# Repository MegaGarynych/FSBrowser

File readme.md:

# FSBrowser

### This project is discontinued. I recommend you to go to [FSBrowserNG](https://github.com/gmag11/FSBrowserNG). It has same functionality and uses a faster web server library.

## Introduction
I wanted to add a standard environment for all my ESP8266 based projects to be able to configure them via web browser to avoid code editing when I need to change some settings like SSID, password, etc.

I found [John Lassen's WebConfig project](http://www.john-lassen.de/index.php/projects/esp-8266-arduino-ide-webconfig) to almost fit my needs. It uses a simple but powerful web interface with dynamic data using [microAJAX](https://code.google.com/archive/p/microajax/). I've added some dynamic data using [Links2004](https://github.com/Links2004)'s [WebSockets library](https://github.com/Links2004/arduinoWebSockets).

So, I tried to fork it. Original WebConfig project stores web pages on PROGMEM, but I was recently using SPIFFS on ESP8266 and I think it is a good way to store web content. I found I was not the first to think this when I noticed about [FSBrowser](https://github.com/esp8266/Arduino/tree/master/libraries/ESP8266WebServer/examples/FSBrowser) example in [ESP8266WebServer](https://github.com/esp8266/Arduino/tree/master/libraries/ESP8266WebServer) library.

This example code has a great bonus. A text editor (based on [ACE](https://ace.c9.io/)) with syntax highligth that can be used to edit html on board directly. I found a [bug](https://github.com/esp8266/Arduino/pull/1771) on it (already sent to [esp8266/Arduino](https://github.com/esp8266/Arduino/) repository) and, when fixed, noticed how usefull this editor is.

My code is a fork of both projects, and has become a start framework for my future projects.

I only have to add more HTML data and some funtions to show dynamic data in order to adapt it to any other task.

It has integrated NTP syncronization based on my own [NTPClient library](https://github.com/gmag11/NtpClient), that can be configured via this Web interface too.

Configuration is stored on SPIFFS too, in a JSON file. So, it recovers config during boot.

Implemented OTA Update with Arduino IDE and Web interface.

Web access can be protected with Basic HTTP Authentication.

#### Notice that Basic HTTP Authentication alone is not suitable to protect data over Internet. It allows recovery of user and password via sniffing and does not encrypt data flow. It is valid to give a first protection and may be a good solution combining it with strong VPN. Take this in account when connecting it to public networks or Internet.

## WiFi connection
I've implemented a way to turn ESP8266 into AP mode so I can set WiFi config when prior WiFi is not available. It is done by setting IO pin 4 to high status during boot. This pin is configurable by a `#define.` __You must ensure it is connected to GND to allow it to connect to a router__.

AP Mode is also started when `loadConfig()` finds no config file (config.json). This is so to help first use without needind to hardcode user and password.

WiFi connection to router is confirmed via LED on IO pin #0 as soon an IP address is got. Same LED is used to confirm AP mode by flashing 3 times. LED ping can be configured in `config.h`.

## Schematics

## How to use it

After compile and flash into ESP8266 you need to upload SPIFFS data using [download tool](https://github.com/esp8266/arduino-esp8266fs-plugin/releases/download/0.2.0/ESP8266FS-0.2.0.zip) for Arduino IDE. Check [SPIFFS doc](https://github.com/esp8266/Arduino/blob/master/doc/filesystem.md) for details.

* `http://ip_address/admin.html` takes you to main configuration GUI.
* `http://ip_address/edit` contains code editor. Any file stored in SPIFFS may be loaded here and saved using `CTRL+S` command.
* `http://ip_address/update` allows remote update through WEB.
* `http://ip_address/` includes an example info page that shows how to get realtime data from ESP. You may change this to adapt to your project.

## TODO

- ~~HTTP Authentication~~ HTTP Basic authentication implemented. Will try to improve to a more secure mechanism.
- ~~OTA update via web interface~~ MD5 cheching added.
- ~~MD5 check of uploaded firmware~~
- ~~Configuration protection~~
- ~~HTTPS (in evaluation).~~ *Not possible with ESP8266 yet*
- ~~Integration of editor in admin.html~~
- ~~Convert code to classes and try to design a library to add all this functionality easily. *Evaluating if this is worth, but anyway it is not currently a priority*~~ *Check my newer [FSBrowserNG](https://github.com/gmag11/FSBrowserNG) repository*

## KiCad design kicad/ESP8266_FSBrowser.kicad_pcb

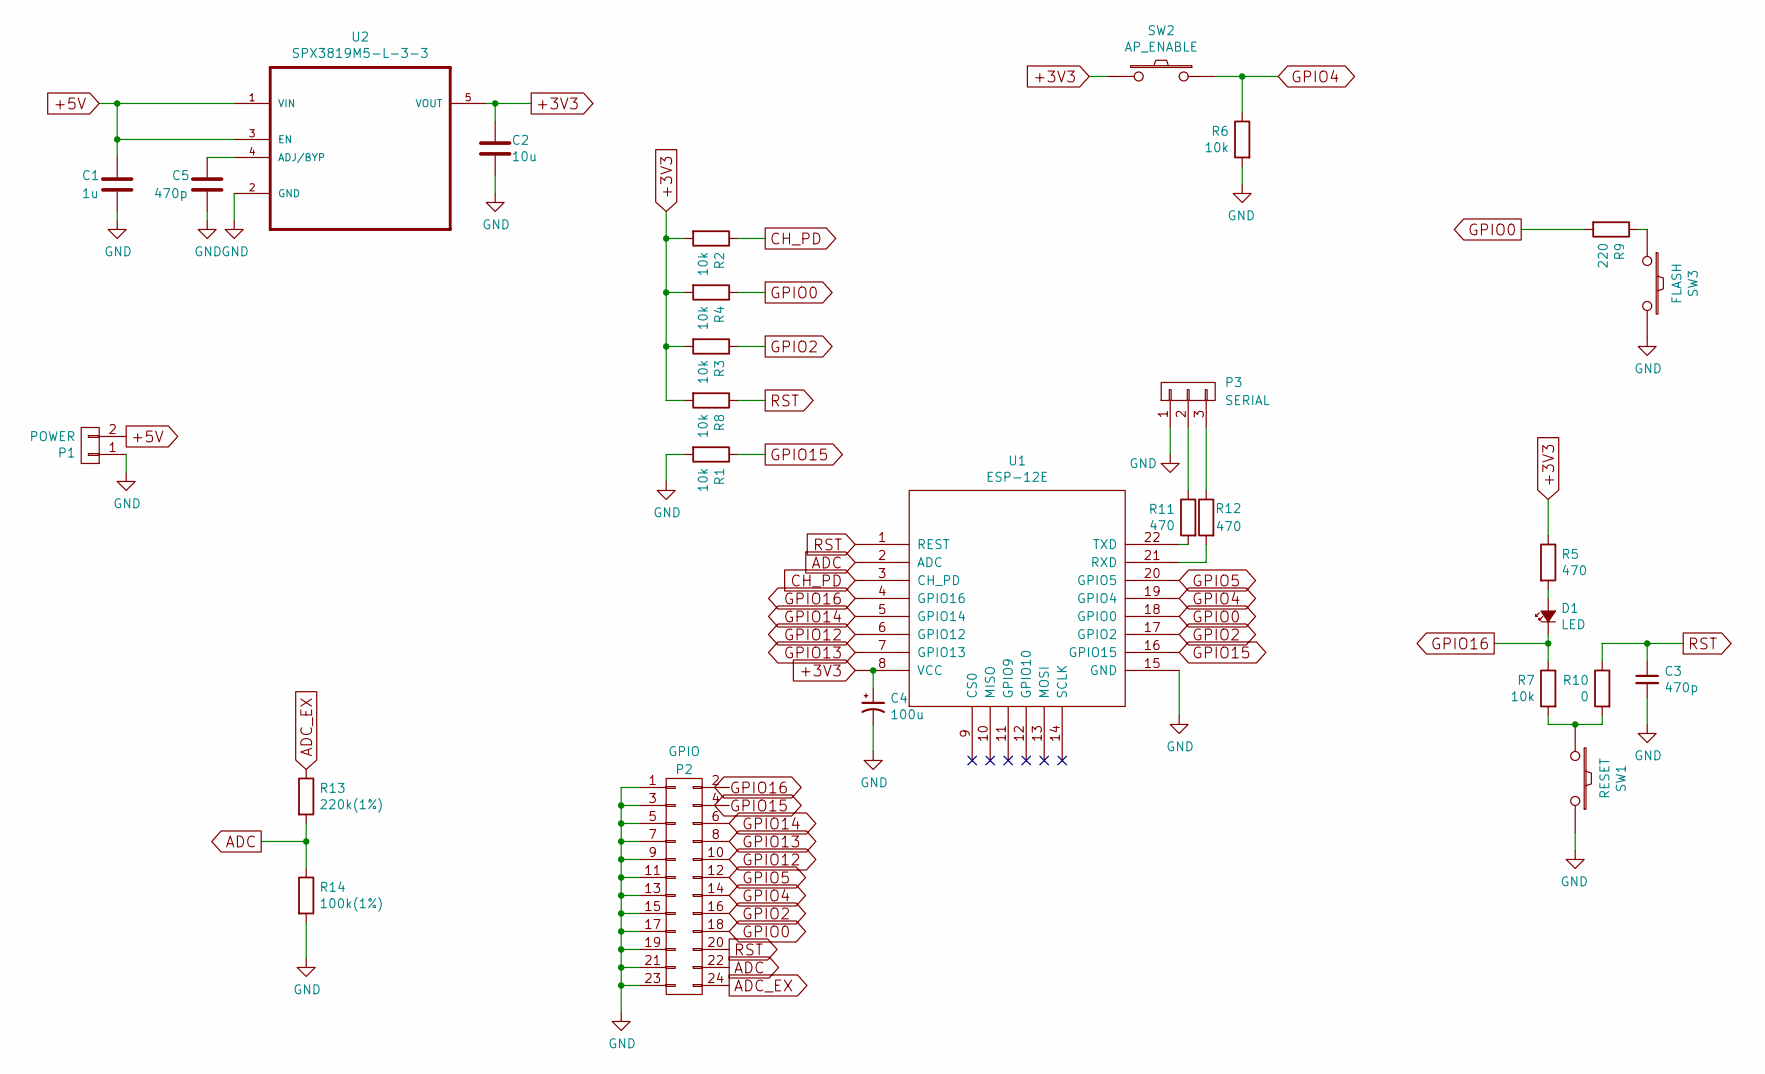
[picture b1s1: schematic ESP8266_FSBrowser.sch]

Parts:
C1: 1u; C_0603
C2: 10u; C_0603
C3, C5: 470p; C_0603
C4: 100u; c_elec_6.3x5.8
D1: LED; LED-3MM
P1: POWER; Pin_Header_Straight_1x02
P2: GPIO; Pin_Header_Straight_2x12
P3: SERIAL; Pin_Header_Straight_1x03
R1, R2, R3, R4, R6, R7, R8: 10k; R_0603
R5, R11, R12: 470; R_0603
R9: 220; R_0603
R10: 0; R_0603
R13: 220k(1%); R_0603
R14: 100k(1%); R_0603
SW1: RESET; SW_SPST_B3S-1000
SW2: AP_ENABLE; SW_SPST_B3S-1000
SW3: FLASH; SW_SPST_B3S-1000
U1: ESP-12E
U2: SPX3819M5-L-3-3; SOT-23-5

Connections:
+3V3: C2.1, R2.2, R3.2, R4.2, R5.1, R8.2, SW2.2, U1.8 (VCC), U2.5 (VOUT)
+5V: C1.1, P1.2, U2.1 (VIN), U2.3 (EN)
ADC: P2.22, R13.2, R14.1, U1.2 (ADC)
ADC_EX: P2.24, R13.1
CH_PD: R2.1, U1.3 (CH_PD)
GND: C1.2, C2.2, C3.2, C4.2, C5.2, P1.1, P2.1, P2.3, P2.5, P2.7, P2.9, P2.11, P2.13, P2.15, P2.17, P2.19, P2.21, P2.23, P3.1, R1.2, R6.2, R14.2, SW1.1, SW3.2, U1.15 (GND), U2.2 (GND)
GPIO0: P2.18, R4.1, R9.2, U1.18 (GPIO0)
GPIO2: P2.16, R3.1, U1.17 (GPIO2)
GPIO4: P2.14, R6.1, SW2.1, U1.19 (GPIO4)
GPIO5: P2.12, U1.20 (GPIO5)
GPIO12: P2.10, U1.6 (GPIO12)
GPIO13: P2.8, U1.7 (GPIO13)
GPIO14: P2.6, U1.5 (GPIO14)
GPIO15: R1.1, U1.16 (GPIO15)
GPIO16: D1.1 (K), R7.1, U1.4 (GPIO16)
unnamed: C5.1, U2.4 (ADJ/BYP)
unnamed: D1.2 (A), R5.2
unnamed: P3.2, R11.1
unnamed: P3.3, R12.1
unnamed: R9.1, SW3.1
unnamed: R7.2, R10.2, SW1.2
unnamed: R11.2, U1.22 (TXD)
unnamed: R12.2, U1.21 (RXD)
RST: C3.1, P2.20, R8.1, R10.1, U1.1 (REST)

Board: 2 copper layers, 28 parts (0 on the bottom side), 24 nets, no tracks yet.

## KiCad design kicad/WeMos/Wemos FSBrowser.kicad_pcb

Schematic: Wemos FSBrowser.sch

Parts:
P1: POWER; Pin_Header_Straight_1x02
P2: TEMP_SENS; Pin_Header_Straight_1x03
R1: 10k; Resistor_Horizontal_RM7mm
R2: 4k7; Resistor_Horizontal_RM7mm
SW1: AP_MODE; SW_SPST_B3S-1000
U1: WeMos_mini; D1_mini_board

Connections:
+3V3: P2.1, R2.1, SW1.2, U1.16
/+5V: P1.2, U1.1
GND: P1.1, P2.3, R1.2, U1.2
GPIO4: R1.1, SW1.1, U1.5
GPIO12: P2.2, R2.2, U1.13

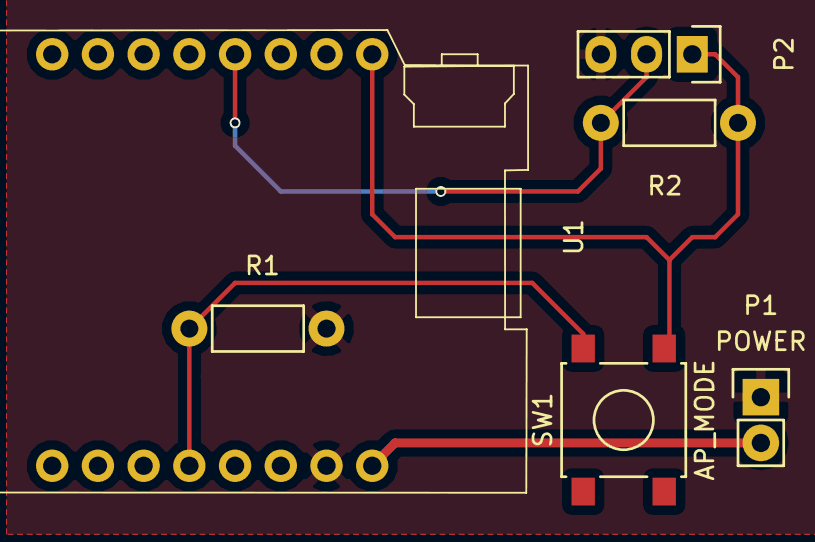
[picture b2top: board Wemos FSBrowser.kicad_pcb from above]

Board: 2 copper layers, 6 parts (0 on the bottom side), 5 nets.

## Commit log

2016-03-05 Connection control
2016-03-05 no message
2016-03-11 Remove AP in startup. It's difficult to do simultaneous AP + STA when there are conncetion problems due to channel scan.
2016-03-11 Clean up disabled functions and variables
2016-03-13 Add WebSocket to send time and date in real time. It works!!!
2016-03-13 Fix editor
2016-03-14 Fix HTML files. Fix editor
2016-03-14 Add more fields to info page
2016-03-14 Update default config
2016-03-14 Reenable AP config if Digital Input 4 is high to be able to reset configuration in case of wrong WiFi configuration
2016-03-15 Add some comments to functions and variables. Filter debug strings with preprocessor directives.
2016-03-26 Add flash function to be used when AP mode
2016-03-26 Add readme.md
2016-03-27 Fix MDNS
2016-03-28 Add schematics
2016-03-28 Add Fritzing breadboard image
2016-04-02 Adjust SPIFFS
2016-04-02 Review html forms. Fix navigation button
2016-04-02 Add built in LED support
2016-04-02 Recover external LED
2016-04-02 Implement OTA Update
2016-04-04 Reconnect websocket when clicking refresh button
2016-04-04 Add remote restart
2016-04-04 Add dim LED
2016-04-05 Return to fix LED. Add flash when disconnected.
2016-04-05 First Basic HTTP Authentication implementation
2016-04-05 Authenticate all
2016-04-05 Filter DEBUG messages
2016-04-06 Store user and passwd on SPIFFS
2016-04-06 Add restart option
2016-04-06 Fix JSON secret example file
2016-04-06 Add link to editor
2016-04-06 Disable HTTP auth if some error ocurrs reading secret file
2016-04-07 Add HTTP Auth config to Web interface
2016-04-07 Fix auth data completion via web interface
2016-04-08 Try configurable LED. Commented lines
2016-04-08 Add led activity when send file to web browser
2016-04-08 Disable OTA password due to Arduino IDE not asking for it
2016-04-08 Implement HTTP update server
2016-04-10 Disable update auth
2016-04-10 Integrate HTTP Updater on server code. TODO: Check if update is possible before uploading. i.e. ESP01 does not allow remote update due to limited flash space.
2016-04-11 Check remote update is possible in this board
2016-04-11 Make DEBUG directives file specific
2016-04-11 Comment code
2016-04-11 Add config protection. Config files are not available to download trhu web browser --> Error 401 Unauthorized.
2016-04-11 Comment more code
2016-04-13 Specific code for ESP01. OTA not possible. Integrated LED connected to TX and only pins 0 and 2 available
2016-04-14 add OTA update to system.html
2016-04-14 Correct navigation
2016-04-14 Correct free space check before web OTA update
2016-04-14 Correct button width
2016-04-14 Add MD5 library
2016-04-14 Add MD5 processing when updating firmware
2016-04-15 Complete MD5 for update
2016-04-15 Restructure DEBUG directives
2016-04-15 Adjust MD5 stuff
2016-04-15 Link OTA password to HTTP secret
2016-04-15 Add compiled file
2016-04-16 Add device name update
2016-04-16 Start AP mode if error loading config
2016-04-16 Fix debug function
2016-04-16 Link HTTP password to WiFiAP
2016-04-16 Remove secret.json from git. Recreated in runtime
2016-04-16 Init http auth data
2016-04-16 Manage device name update
2016-04-19 Rearrange buttons
2016-04-19 Work on MD5 checking
2016-04-19 Add save button
2016-04-19 MD5 OTA check working
2016-04-20 Handle general.html correctly
2016-04-20 Handle general,html correctly
2016-04-20 Fix OTA web update
2016-04-20 Add save, undo and redo buttons to editor
2016-04-20 Remove old code
2016-04-20 Update build file
2016-04-20 Change editor theme to dark
2016-04-20 Hide password field
2016-04-20 Change editor theme
2016-04-20 Add "restarting" text after update
2016-04-20 Add more detail to update.html
2016-04-20 Add screenshots
2016-07-26 Fix lower case file names handling
2016-07-27 Delay before restart
2016-07-27 Update ACE Editor to latest version
2016-08-04 Add Kicad project
2016-08-05 Start porting to ESPAsyncWebServer
2016-08-07 Server working. WebOTA still fails.
2016-08-07 Fix OTA
2016-08-07 Reorder mdns init
2016-08-08 AsyncWebSocket migration
2016-08-08 Fix Upload
2016-08-08 Fix websocket javascript code
2016-08-08 Gzip not working. Temporary fix
2016-08-08 Try Async WiFi Scan
2016-08-08 Revert "Try Async WiFi Scan"
    This reverts commit 8a699e1ab9fc6154d9e79e20cc89a91f113873b7.
2016-08-09 Debug Gzip Upload
2016-08-09 Change case to if else
2016-08-09 Fix `printf()`
2016-08-10 Fix gzip encodding support
2016-08-10 Avoid filename chunking
2016-08-10 Remove annoying time date debug output
2016-08-10 Add WeMos adapter
2016-08-10 Remove .bak files
2016-08-13 Play with kicad files
2016-08-13 Revert "Play with kicad files"
    This reverts commit 04bb3029db1baf8c5355bf4588b1dad35f342a4f.
2016-08-13 Revert "Revert "Play with kicad files""
    This reverts commit 6e753d2bf345cea2ba5e5adde0968fd2950895fa.
2016-08-26 Update NTP library usage
